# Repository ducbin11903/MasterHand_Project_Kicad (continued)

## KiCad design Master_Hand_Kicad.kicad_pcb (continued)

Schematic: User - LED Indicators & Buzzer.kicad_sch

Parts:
D9, D15, D16: RED 0402; LED0402-R-RD; MPN YLED0402G; LCSC Part C20608784
D10: ORANGE 0402; LED0402-R-RD; MPN YLED0402G; LCSC Part C20608784
D11: YELLOW 0402; LED0402-R-RD; MPN YLED0402G; LCSC Part C20608784
D12: GREEN 0402; LED0402-R-RD; MPN YLED0402G; LCSC Part C20608784
D13: BLUE 0402; LED0402-R-RD; MPN YLED0402G; LCSC Part C20608784
D14: WHITE 0402; LED0402-R-RD; MPN YLED0402G; LCSC Part C20608784
R59, R60, R65, R66: 330R 0.1%; R0402; MPN RT0402FRE07100KL; LCSC Part C728576
R61, R62, R63, R64: 100R 0.1%; R0402; MPN RT0402FRE07100KL; LCSC Part C728576

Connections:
+3V3: D9.1 (A), D10.1 (A), D11.1 (A), D12.1 (A), D13.1 (A), D14.1 (A), D15.1 (A), D16.1 (A); also elsewhere on the board
/Project Architecture/MCU - IOs/GPIO-LED_Debug_1: R65.1; also elsewhere on the board
/Project Architecture/MCU - IOs/GPIO-LED_Debug_2: R66.1; also elsewhere on the board
/Project Architecture/MCU - IOs/GPIO-LED_I: R59.1; also elsewhere on the board
/Project Architecture/MCU - IOs/GPIO-LED_M: R64.1; also elsewhere on the board
/Project Architecture/MCU - IOs/GPIO-LED_P: R62.1; also elsewhere on the board
/Project Architecture/MCU - IOs/GPIO-LED_R: R63.1; also elsewhere on the board
/Project Architecture/MCU - IOs/GPIO-LED_T1: R60.1; also elsewhere on the board
/Project Architecture/MCU - IOs/GPIO-LED_T2: R61.1; also elsewhere on the board
unnamed: D9.2 (K), R59.2
unnamed: D10.2 (K), R60.2
unnamed: D11.2 (K), R61.2
unnamed: D12.2 (K), R62.2
unnamed: D13.2 (K), R63.2
unnamed: D14.2 (K), R64.2
unnamed: D15.2 (K), R65.2
unnamed: D16.2 (K), R66.2

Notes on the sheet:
[${#}] ${SHEETNAME}

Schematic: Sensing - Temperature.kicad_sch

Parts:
C95: 100nF 50V; C0402; MPN CC0402KRX5R7BB105; LCSC Part C325464
R67, R68: 10K 0.1%; R0402; MPN RT0402FRE07100KL; LCSC Part C728576
U16: SHT40-N-NF; DFN-4_L1.5-W1.5-P0.80-TL-EP; MPN SHT40-N-NF; LCSC Part C54946589

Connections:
+3V3: C95.2, R67.1, R68.1, U16.3 (VDD); also elsewhere on the board
/Project Architecture/MCU - IOs/I2C-SCL: R68.2, U16.2 (SCL); also elsewhere on the board
/Project Architecture/MCU - IOs/I2C-SDA: R67.2, U16.1 (SDA); also elsewhere on the board
GND: C95.1, U16.4 (VSS); also elsewhere on the board

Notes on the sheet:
[${#}] ${SHEETNAME}

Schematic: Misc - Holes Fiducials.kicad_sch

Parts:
FM1, FM2, FM3: Fiducial_1mm_Mask2mm
H1, H2, H3: M2.4; MountingHole_2.4mm_M2.4_Pad_Via

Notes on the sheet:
[${#}] ${SHEETNAME}
Mounting Holes and Fiducial Markers

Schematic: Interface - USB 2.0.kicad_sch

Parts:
C83, C85: 4.7uF 50V; C0603; MPN CAP CER 0603; LCSC Part C14663
C84, C86: 100nF 50V; C0402; MPN CC0402KRX5R7BB105; LCSC Part C325464
D2, D5: BLUE 0402; LED0402-R-RD; MPN YLED0402G; LCSC Part C20608784
D3, D6: SMAJ5.0A; SMA_L4.3-W2.6-LS5.2-RD; MPN SMAJ5.0A; LCSC Part C83329
D4, D7: USBLC6-2SC6; SOT-23-6_L2.9-W1.6-P0.95-LS2.8-BL; MPN USBLC6-2SC6; LCSC Part C2827654
J9, J10: TYPE-C 16PIN 2MD; USB-C-SMD_TYPE-C-16PIN-2MD-073; MPN TYPE-C 16PIN 2MD(073); LCSC Part C2765186
R43, R48: 430K 0.1%; R0402; MPN RT0402FRE07100KL; LCSC Part C728576
R44, R49: 620K 0.1%; R0402; MPN RT0402FRE07100KL; LCSC Part C728576
R45, R50: 1K 0.1%; R0402; MPN RT0402FRE07100KL; LCSC Part C728576
R46, R47, R51, R52: 5.1K 0.1%; R0402; MPN RT0402FRE07100KL; LCSC Part C728576

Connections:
/Project Architecture/Interface - USB 2.0/USB1_N: D4.4 (IO2); also elsewhere on the board
/Project Architecture/Interface - USB 2.0/USB1_P: D4.6 (IO1); also elsewhere on the board
/Project Architecture/Interface - USB 2.0/USB2_N: D7.6 (IO1); also elsewhere on the board
/Project Architecture/Interface - USB 2.0/USB2_P: D7.4 (IO2); also elsewhere on the board
/Project Architecture/Interface - USB 2.0/VBUS_1: C83.2, C84.1, D3.1 (C), D4.5 (VBUS), J9.A4B9 (VBUS), J9.B4A9 (VBUS), R43.1, R45.1
/Project Architecture/Interface - USB 2.0/VBUS_2: C85.2, C86.1, D6.1 (C), D7.5 (VBUS), J10.A4B9 (VBUS), J10.B4A9 (VBUS), R48.1, R50.1
/Project Architecture/Interface - USB 2.0/VBUS_DET1: R43.2, R44.1; also elsewhere on the board
/Project Architecture/Interface - USB 2.0/VBUS_DET2: R48.2, R49.1; also elsewhere on the board
GND: C83.1, C84.2, C85.1, C86.2, D2.2 (K), D3.2 (A), D4.2 (GND), D5.2 (K), D6.2 (A), D7.2 (GND), J9.13 (EH), J9.14 (EH), J9.A1B12 (GND), J9.B1A12 (GND), J10.13 (EH), J10.14 (EH), J10.A1B12 (GND), J10.B1A12 (GND), R44.2, R46.2, R47.2, R49.2, R51.2, R52.2; also elsewhere on the board
unnamed: D2.1 (A), R45.2
unnamed: D5.1 (A), R50.2
unnamed: J9.A5 (CC1), R46.1
unnamed: J9.B5 (CC2), R47.1
unnamed: D4.3 (IO2), J9.A7 (Dn1), J9.B7 (Dn2)
unnamed: D4.1 (IO1), J9.A6 (Dp1), J9.B6 (Dp2)
unnamed: J10.A5 (CC1), R51.1
unnamed: J10.B5 (CC2), R52.1
unnamed: D7.1 (IO1), J10.A7 (Dn1), J10.B7 (Dn2)
unnamed: D7.3 (IO2), J10.A6 (Dp1), J10.B6 (Dp2)

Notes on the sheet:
[${#}] ${SHEETNAME}
DESIGN NOTE: [1] VBUS NOT connected to +5V/+3V3. Board is self-powered(LiPo). Sense + LED only. No backfeed to host. [2] LED direct from VBUS @ 1mA. USB2.0 suspend limit 2.5mA. LED 1mA + divider 33uA = 1.03mA (41%). Do NOT raise to 5mA. [3] VBUS_DET required - G474 has no dedicated VBUS pin. Self-p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

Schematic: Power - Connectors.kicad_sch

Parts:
C1, C2, C3, C4: 100nF 50V; C0603; MPN CAP CER 0603; LCSC Part C14663
J1: XT30PW-F; CONN-TH_XT30PW-F-1; MPN XT30PW-F20.G.Y; LCSC Part C2913282
J2: KF350-3.5-2P; CONN-TH_P3.50_KF350-3.5-2P; MPN KF350-3.5-2P; LCSC Part C474892
Q1, Q2: HV10N03; SOT-89-3_L4.5-W2.5-P1.50-LS4.0-BR; MPN HV10N03; LCSC Part C53329063
U1, U2: LM74700QDBVRQ1; SOT-23-6_L2.9-W1.6-P0.95-LS2.8-BL; MPN LM74700QDBVRQ1; LCSC Part C2941042

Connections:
+VBAT: Q1.3 (S), Q2.3 (S), U1.4 (CATHODE), U2.4 (CATHODE); also elsewhere on the board
/Project Architecture/Power - Connectors/+V_ADAPTER: C3.1, C4.1, J2.2, Q2.2 (D), U2.3 (EN), U2.6 (ANODE)
/Project Architecture/Power - Connectors/+V_BAT2S: C1.1, C2.1, J1.1, Q1.2 (D), U1.3 (EN), U1.6 (ANODE)
GND: C1.2, C3.2, J1.2, J2.1, U1.2 (GND), U2.2 (GND); also elsewhere on the board
unnamed: Q1.1 (G), U1.5 (GATE)
unnamed: Q2.1 (G), U2.5 (GATE)
unnamed: C2.2, U1.1 (VCAP)
unnamed: C4.2, U2.1 (VCAP)

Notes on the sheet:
[${#}] ${SHEETNAME}
Power Connectors - Path Control

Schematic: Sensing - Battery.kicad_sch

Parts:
C97: 100nF 50V; C0402; MPN CC0402KRX5R7BB105; LCSC Part C325464
R71: 100K 0.1%; R0402; MPN RT0402FRE07100KL; LCSC Part C728576
R72: 47K 0.1%; R0402; MPN RT0402FRE07100KL; LCSC Part C728576

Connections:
+VBAT: R71.2; also elsewhere on the board
/Project Architecture/MCU - IOs/SENSE_VBAT: C97.2, R71.1, R72.2; also elsewhere on the board
GND: C97.1, R72.1; also elsewhere on the board

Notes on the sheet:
Battery Voltage Sensing
[${#}] ${SHEETNAME}
DESIGN NOTE: Battery voltage sensing divider for 2S LiPo battery. R1 = 100kΩ (Top) R2 = 47kΩ (Bottom) Divider Ratio: VADC = VBAT × (47 / (100 + 47)) VADC = VBAT × 0.3197 2S LiPo: Max battery voltage (8.4V): 2.69 V Nominal voltage (7.4V): 2.37 V Low battery voltage (6.4V): 2.05 V Cutoff voltage (6.0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

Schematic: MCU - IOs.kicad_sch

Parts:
C43, C44, C45, C46: 8pF 16V; C0402; MPN CC0402KRX5R7BB105; LCSC Part C325464
U6, U7: STM32G474RET6; LQFP-64_L10.0-W10.0-P0.50-LS12.0-BL; MPN STM32G474RET6; LCSC Part C521608
X1, X2: X322516MLB4SI; CRYSTAL-SMD_4P-L3.2-W2.5-BL; MPN X322516MLB4SI; LCSC Part C13738

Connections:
/Project Architecture/Interface - FD-CAN/FDCAN1_RX: U6.34 (PB12); also elsewhere on the board
/Project Architecture/Interface - FD-CAN/FDCAN1_TX: U6.35 (PB13); also elsewhere on the board
/Project Architecture/Interface - FD-CAN/FDCAN2_RX: U7.34 (PB12); also elsewhere on the board
/Project Architecture/Interface - FD-CAN/FDCAN2_TX: U7.35 (PB13); also elsewhere on the board
/Project Architecture/Interface - Interconnects/NRST1: U6.7 (PG10); also elsewhere on the board
/Project Architecture/Interface - Interconnects/NRST2: U7.7 (PG10); also elsewhere on the board
/Project Architecture/Interface - Interconnects/SWCLK1: U6.50 (PA14); also elsewhere on the board
/Project Architecture/Interface - Interconnects/SWCLK2: U7.50 (PA14); also elsewhere on the board
/Project Architecture/Interface - Interconnects/SWDIO1: U6.49 (PA13); also elsewhere on the board
/Project Architecture/Interface - Interconnects/SWDIO2: U7.49 (PA13); also elsewhere on the board
/Project Architecture/Interface - Interconnects/USART1_CK1: U6.54 (PC12); also elsewhere on the board
/Project Architecture/Interface - Interconnects/USART1_CK2: U7.54 (PC12); also elsewhere on the board
/Project Architecture/Interface - Interconnects/USART1_RX1: U6.33 (PB11); also elsewhere on the board
/Project Architecture/Interface - Interconnects/USART1_RX2: U7.33 (PB11); also elsewhere on the board
/Project Architecture/Interface - Interconnects/USART1_TX1: U6.30 (PB10); also elsewhere on the board
/Project Architecture/Interface - Interconnects/USART1_TX2: U7.30 (PB10); also elsewhere on the board
/Project Architecture/Interface - USB 2.0/USB1_N: U6.45 (PA11); also elsewhere on the board
/Project Architecture/Interface - USB 2.0/USB1_P: U6.46 (PA12); also elsewhere on the board
/Project Architecture/Interface - USB 2.0/USB2_N: U7.45 (PA11); also elsewhere on the board
/Project Architecture/Interface - USB 2.0/USB2_P: U7.46 (PA12); also elsewhere on the board
/Project Architecture/Interface - USB 2.0/VBUS_DET1: U6.44 (PA10); also elsewhere on the board
/Project Architecture/Interface - USB 2.0/VBUS_DET2: U7.44 (PA10); also elsewhere on the board
/Project Architecture/MCU - IOs/BOARD_VERSION: U6.26 (PB2); also elsewhere on the board
/Project Architecture/MCU - IOs/BOOT_1: U6.61 (PB8); also elsewhere on the board
/Project Architecture/MCU - IOs/BOOT_2: U7.61 (PB8); also elsewhere on the board
/Project Architecture/MCU - IOs/DIAG_I: U6.3 (PC14); also elsewhere on the board
/Project Architecture/MCU - IOs/DIAG_M: U7.3 (PC14); also elsewhere on the board
/Project Architecture/MCU - IOs/DIAG_P: U7.37 (PB15); also elsewhere on the board
/Project Architecture/MCU - IOs/DIAG_R: U7.55 (PD2); also elsewhere on the board
/Project Architecture/MCU - IOs/DIAG_T1: U6.55 (PD2); also elsewhere on the board
/Project Architecture/MCU - IOs/DIAG_T2: U6.37 (PB15); also elsewhere on the board
/Project Architecture/MCU - IOs/ECA_I: U6.12 (PA0); also elsewhere on the board
/Project Architecture/MCU - IOs/ECA_M: U7.12 (PA0); also elsewhere on the board
/Project Architecture/MCU - IOs/ECA_P: U7.38 (PC6); also elsewhere on the board
/Project Architecture/MCU - IOs/ECA_R: U7.59 (PB6); also elsewhere on the board
/Project Architecture/MCU - IOs/ECA_T1: U6.59 (PB6); also elsewhere on the board
/Project Architecture/MCU - IOs/ECA_T2: U6.38 (PC6); also elsewhere on the board
/Project Architecture/MCU - IOs/ECB_I: U6.13 (PA1); also elsewhere on the board
/Project Architecture/MCU - IOs/ECB_M: U7.13 (PA1); also elsewhere on the board
/Project Architecture/MCU - IOs/ECB_P: U7.39 (PC7); also elsewhere on the board
/Project Architecture/MCU - IOs/ECB_R: U7.60 (PB7); also elsewhere on the board
/Project Architecture/MCU - IOs/ECB_T1: U6.60 (PB7); also elsewhere on the board
/Project Architecture/MCU - IOs/ECB_T2: U6.39 (PC7); also elsewhere on the board
/Project Architecture/MCU - IOs/ECC_I: U6.10 (PC2); also elsewhere on the board
/Project Architecture/MCU - IOs/ECC_M: U7.10 (PC2); also elsewhere on the board
/Project Architecture/MCU - IOs/ECC_P: U7.21 (PA7); also elsewhere on the board
/Project Architecture/MCU - IOs/ECC_R: U7.18 (PA4); also elsewhere on the board
/Project Architecture/MCU - IOs/ECC_T1: U6.18 (PA4); also elsewhere on the board
/Project Architecture/MCU - IOs/ECC_T2: U6.21 (PA7); also elsewhere on the board
/Project Architecture/MCU - IOs/EN_I: U6.9 (PC1); also elsewhere on the board
/Project Architecture/MCU - IOs/EN_M: U7.9 (PC1); also elsewhere on the board
/Project Architecture/MCU - IOs/EN_P: U7.23 (PC5); also elsewhere on the board
/Project Architecture/MCU - IOs/EN_R: U7.20 (PA6); also elsewhere on the board
/Project Architecture/MCU - IOs/EN_T1: U6.20 (PA6); also elsewhere on the board
/Project Architecture/MCU - IOs/EN_T2: U6.23 (PC5); also elsewhere on the board
/Project Architecture/MCU - IOs/GPIO-LED_Debug_1: U6.25 (PB1); also elsewhere on the board
/Project Architecture/MCU - IOs/GPIO-LED_Debug_2: U7.25 (PB1); also elsewhere on the board
/Project Architecture/MCU - IOs/GPIO-LED_I: U6.51 (PA15); also elsewhere on the board
/Project Architecture/MCU - IOs/GPIO-LED_M: U7.51 (PA15); also elsewhere on the board
/Project Architecture/MCU - IOs/GPIO-LED_P: U7.62 (PB9); also elsewhere on the board
/Project Architecture/MCU - IOs/GPIO-LED_R: U7.58 (PB5); also elsewhere on the board
/Project Architecture/MCU - IOs/GPIO-LED_T1: U6.58 (PB5); also elsewhere on the board
/Project Architecture/MCU - IOs/GPIO-LED_T2: U6.62 (PB9); also elsewhere on the board
/Project Architecture/MCU - IOs/I2C-SCL: U7.43 (PA9); also elsewhere on the board
/Project Architecture/MCU - IOs/I2C-SDA: U7.42 (PA8); also elsewhere on the board
/Project Architecture/MCU - IOs/MCU_ID1: U6.2 (PC13); also elsewhere on the board
/Project Architecture/MCU - IOs/MCU_ID2: U7.2 (PC13); also elsewhere on the board
/Project Architecture/MCU - IOs/OCM_I: U6.8 (PC0); also elsewhere on the board
/Project Architecture/MCU - IOs/OCM_M: U7.8 (PC0); also elsewhere on the board
/Project Architecture/MCU - IOs/OCM_P: U7.22 (PC4); also elsewhere on the board
/Project Architecture/MCU - IOs/OCM_R: U7.19 (PA5); also elsewhere on the board
/Project Architecture/MCU - IOs/OCM_T1: U6.19 (PA5); also elsewhere on the board
/Project Architecture/MCU - IOs/OCM_T2: U6.22 (PC4); also elsewhere on the board
/Project Architecture/MCU - IOs/OSC-IN_1: C43.1, U6.5 (PF0), X1.1 (OSC1)
/Project Architecture/MCU - IOs/OSC-IN_2: C45.1, U7.5 (PF0), X2.1 (OSC1)
/Project Architecture/MCU - IOs/OSC-OUT_1: C44.1, U6.6 (PF1), X1.3 (OSC2)
/Project Architecture/MCU - IOs/OSC-OUT_2: C46.1, U7.6 (PF1), X2.3 (OSC2)
/Project Architecture/MCU - IOs/PWMA_I: U6.17 (PA3); also elsewhere on the board
/Project Architecture/MCU - IOs/PWMA_M: U7.17 (PA3); also elsewhere on the board
/Project Architecture/MCU - IOs/PWMA_P: U7.41 (PC9); also elsewhere on the board
/Project Architecture/MCU - IOs/PWMA_R: U7.56 (PB3); also elsewhere on the board
/Project Architecture/MCU - IOs/PWMA_T1: U6.56 (PB3); also elsewhere on the board
/Project Architecture/MCU - IOs/PWMA_T2: U6.41 (PC9); also elsewhere on the board
/Project Architecture/MCU - IOs/PWMB_I: U6.14 (PA2); also elsewhere on the board
/Project Architecture/MCU - IOs/PWMB_M: U7.14 (PA2); also elsewhere on the board
/Project Architecture/MCU - IOs/PWMB_P: U7.40 (PC8); also elsewhere on the board
/Project Architecture/MCU - IOs/PWMB_R: U7.57 (PB4); also elsewhere on the board
/Project Architecture/MCU - IOs/PWMB_T1: U6.57 (PB4); also elsewhere on the board
/Project Architecture/MCU - IOs/PWMB_T2: U6.40 (PC8); also elsewhere on the board
/Project Architecture/MCU - IOs/SENSE_VBAT: U7.26 (PB2); also elsewhere on the board
/Project Architecture/MCU - IOs/UART_RX: U6.53 (PC11), U7.52 (PC10)
/Project Architecture/MCU - IOs/UART_TX: U6.52 (PC10), U7.53 (PC11)
GND: C43.2, C44.2, C45.2, C46.2, X1.2 (GND), X1.4 (GND), X2.2 (GND), X2.4 (GND); also elsewhere on the board

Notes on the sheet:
MCU 2
MD Pinky
MCU 1
MD Thumb 1
MD Thumb 2
LEDs
USB PORT
MCB to MB - I2C
Battery Voltage Sense
Buzzer
MD Index
Out of Density to Place TP
MD Ring
MD Middle
Temperature and Humidity
SWD (Debug) Port
5Mbps FD-CAN Bus
Board Version Selection
MCU ID
[${#}] ${SHEETNAME}
SWITCH
Motor Driver
DESIGN NOTE: We use the LQFP64 version to have extra pins for controlling an external fan.
LAYOUT NOTE: Footprint deviates from datasheet and IPC7351 to allow for soldermask sliver between pads according to PCBWay design rules.
Oscillator HSE
MCB to MB - USART
Test Points
DESIGN NOTE: Do not forget to flash option bytes when flashing for the first time.

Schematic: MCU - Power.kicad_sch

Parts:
C25, C31, C32, C34, C40, C41: 1uF 16V; C0402; MPN CC0402KRX5R7BB105; LCSC Part C325464
C26, C35: 4.7uF 16V; C0402; MPN CC0402KRX5R7BB105; LCSC Part C325464
C27, C28, C29, C30, C33, C36, C37, C38, C39, C42: 100nF 50V; C0402; MPN CC0402KRX5R7BB105; LCSC Part C325464
FB1, FB2: 1k @ 100MHz; L0805; MPN PBBHAQ2012H-102T10; LCSC Part C52178237
U6, U7: STM32G474RET6; LQFP-64_L10.0-W10.0-P0.50-LS12.0-BL; MPN STM32G474RET6; LCSC Part C521608

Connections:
+3V3: C25.1, C26.1, C27.1, C28.1, C29.1, C30.1, C34.1, C35.1, C36.1, C37.1, C38.1, C39.1, U6.1 (VBAT), U6.16 (VDD), U6.32 (VDD), U6.48 (VDD), U6.64 (VDD), U7.1 (VBAT), U7.16 (VDD), U7.32 (VDD), U7.48 (VDD), U7.64 (VDD); also elsewhere on the board
+A3V3: C31.1, C40.1, FB1.1, FB2.1; also elsewhere on the board
GND: C25.2, C26.2, C27.2, C28.2, C29.2, C30.2, C31.2, C32.2, C33.2, C34.2, C35.2, C36.2, C37.2, C38.2, C39.2, C40.2, C41.2, C42.2, U6.15 (VSS), U6.27 (VSSA), U6.31 (VSS), U6.47 (VSS), U6.63 (VSS), U7.15 (VSS), U7.27 (VSSA), U7.31 (VSS), U7.47 (VSS), U7.63 (VSS); also elsewhere on the board
unnamed: C32.1, C33.1, FB1.2, U6.28 (VREF+), U6.29 (VDDA)
unnamed: C41.1, C42.1, FB2.2, U7.28 (VREF+), U7.29 (VDDA)

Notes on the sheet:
Microcontroller Power Supply Scheme
LAYOUT NOTE: Place each capacitor close to the relevant pin. Minimize loop inductance.

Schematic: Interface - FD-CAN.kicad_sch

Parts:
C87, C88, C89, C90: 100nF 50V; C0402; MPN CC0402KRX5R7BB105; LCSC Part C325464
R53, R54: 10K 0.1%; R0402; MPN RT0402FRE07100KL; LCSC Part C728576
U14, U15: TJA1051T/3; SOP-8_L4.9-W3.9-P1.27-LS6.0-BL-1; MPN TJA1051T/3; LCSC Part C5342108

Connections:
+3V3: C88.1, C90.1, R53.1, R54.2, U14.5 (VIO), U15.5 (VIO); also elsewhere on the board
+5V: C87.1, C89.1, U14.3 (VCC), U15.3 (VCC); also elsewhere on the board
/Project Architecture/Interface - FD-CAN/FDCAN1_RX: U15.4 (RXD); also elsewhere on the board
/Project Architecture/Interface - FD-CAN/FDCAN1_TX: R54.1, U15.1 (TXD); also elsewhere on the board
/Project Architecture/Interface - FD-CAN/FDCAN2_RX: U14.4 (RXD); also elsewhere on the board
/Project Architecture/Interface - FD-CAN/FDCAN2_TX: R53.2, U14.1 (TXD); also elsewhere on the board
/Project Architecture/Interface - FD-CAN/FDCAN_N: U14.6 (CANL), U15.6 (CANL); also elsewhere on the board
/Project Architecture/Interface - FD-CAN/FDCAN_P: U14.7 (CANH), U15.7 (CANH); also elsewhere on the board
GND: C87.2, C88.2, C89.2, C90.2, U14.2 (GND), U14.8 (S), U15.2 (GND), U15.8 (S); also elsewhere on the board

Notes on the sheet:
LAYOUT NOTE: We decided to route it further away to minimize risk of ground lift on the RX/TX lines due to high currents.
DESIGN NOTE: Silent mode disabled. Pin "S" to ground.
Fault Protected FD-CAN Transceiver
LAYOUT NOTE: Place close to FD-CAN connector if possible to reduce stub length.
DESIGN NOTE: 120-ohm termination in Interconnects sheet.
[${#}] ${SHEETNAME}

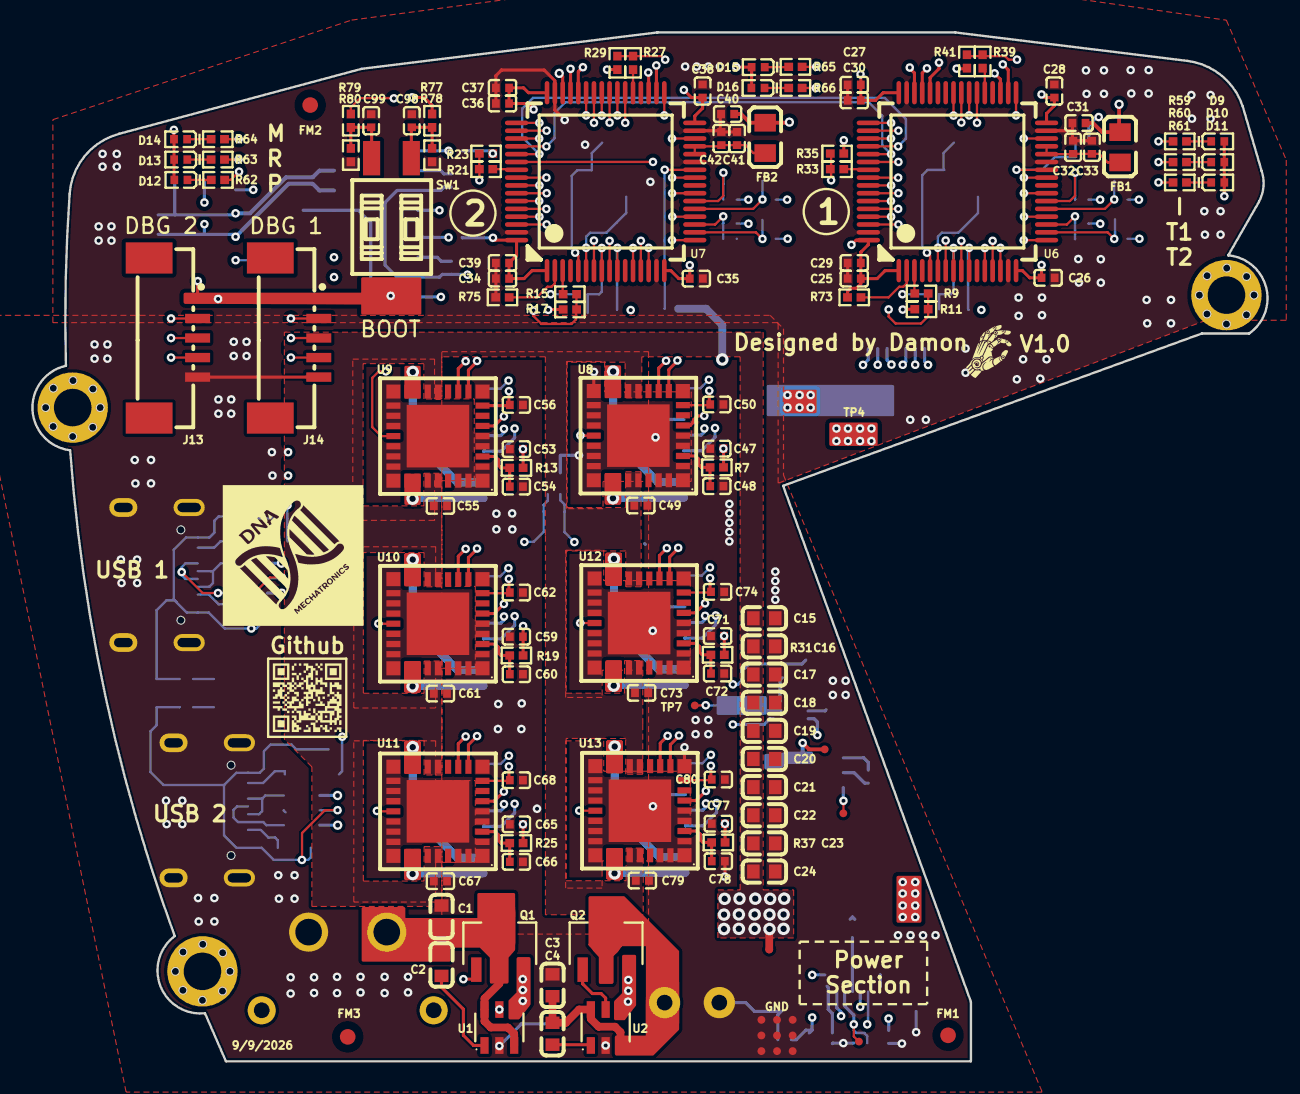
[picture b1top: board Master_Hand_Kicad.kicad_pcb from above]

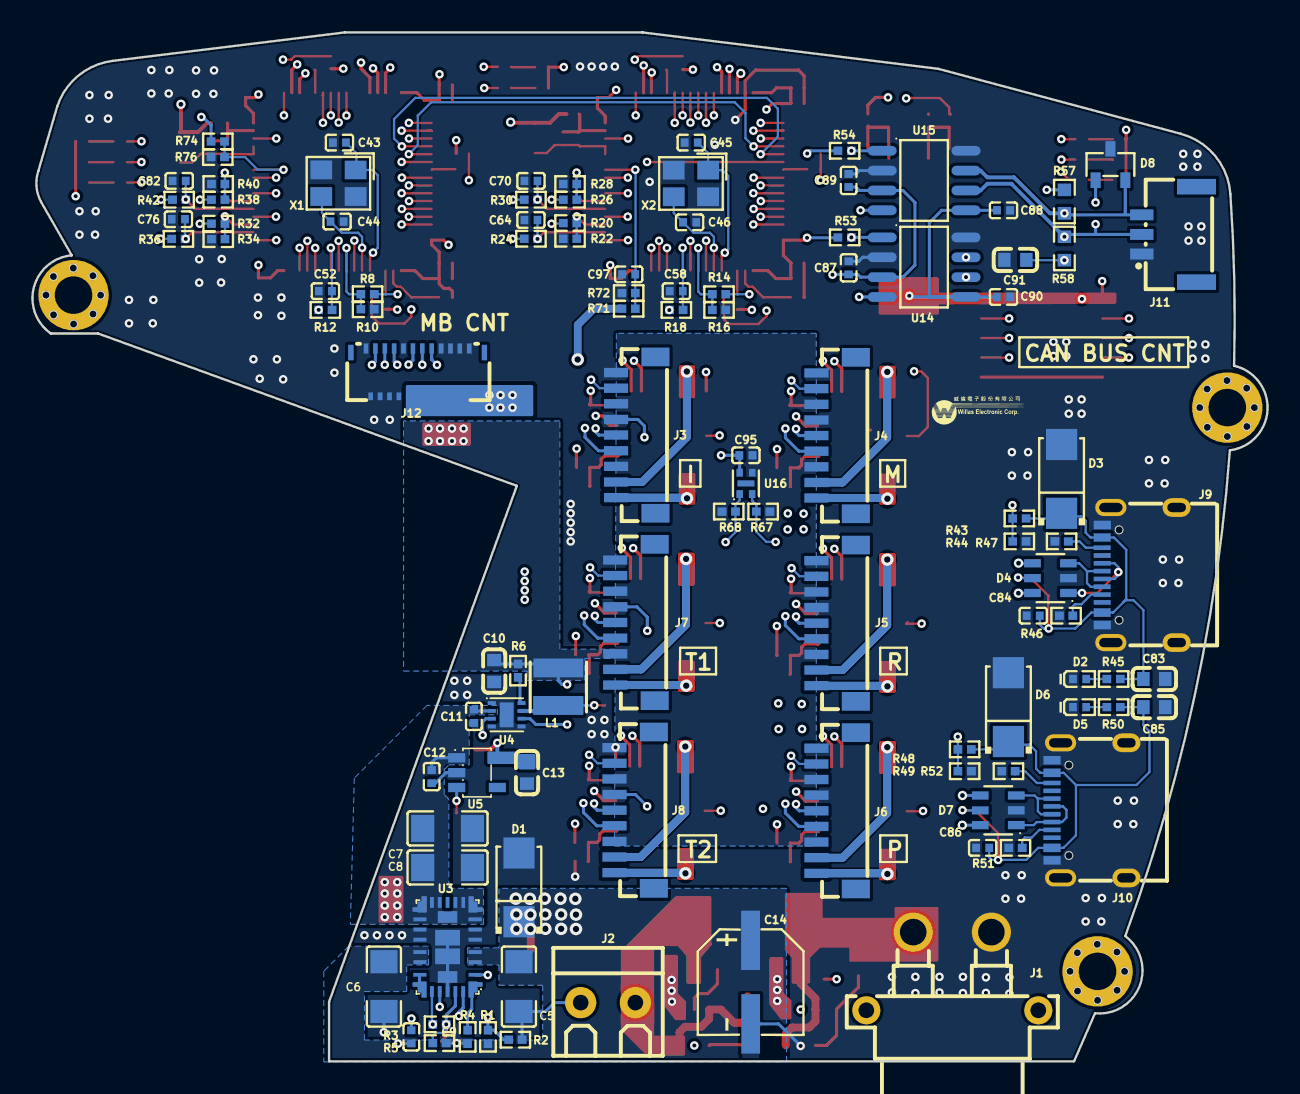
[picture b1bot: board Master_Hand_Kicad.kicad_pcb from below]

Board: 6 copper layers, 79.0 x 65.8 mm, 232 parts (104 on the bottom side), 174 nets.

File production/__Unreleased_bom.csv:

Designator,Footprint,Quantity,Value,LCSC Part #
"C1, C2, C3, C4",C0603,4,100nF 50V,C14663
C10,C0603,1,22uF 50V,C14663
C11,C0402,1,10uF 50V,C325464
"C12, C9",C0402,2,1uF 50V,C325464
C13,C0603,1,1uF 50V,C14663
C14,CAP-SMD_BD6.3-L6.6-W6.6-FD-1,1,SM337M025E0800,C44606382
"C15, C16, C17, C18, C19, C20, C21, C22, C23, C24",C0603,10,10uF 50V,C14663
"C25, C31, C32, C34, C40, C41",C0402,6,1uF 16V,C325464
"C26, C35",C0402,2,4.7uF 16V,C325464
"C27, C28, C29, C30, C33, C36, C37, C38, C39, C42, C48, C49, C52, C54, C55, C58, C60, C61, C64, C66, C67, C70, C72, C73, C76, C78, C79, C82, C84, C86, C87, C88, C89, C90, C95, C97, C98, C99",C0402,38,100nF 50V,C325464
"C43, C44, C45, C46",C0402,4,8pF 16V,C325464
"C47, C53, C59, C65, C71, C77",C0402,6,4.7uF 50V,C325464
"C5, C6",C1206,2,4.7uF 100V,C132170
"C50, C56, C62, C68, C74, C80",C0402,6,470nF 50V,C325464
C7,C1206,1,10uF 50V,C132170
C8,C1206,1,100nF 50V,C132170
"C83, C85, C91",C0603,3,4.7uF 50V,C14663
D1,SMA_L4.3-W2.6-LS5.2-RD,1,SMAJ12A,C148213
D10,LED0402-R-RD,1,ORANGE 0402,C20608784
D11,LED0402-R-RD,1,YELLOW 0402,C20608784
D12,LED0402-R-RD,1,GREEN 0402,C20608784
"D13, D2, D5",LED0402-R-RD,3,BLUE 0402,C20608784
D14,LED0402-R-RD,1,WHITE 0402,C20608784
"D15, D16, D9",LED0402-R-RD,3,RED 0402,C20608784
"D3, D6",SMA_L4.3-W2.6-LS5.2-RD,2,SMAJ5.0A,C83329
"D4, D7",SOT-23-6_L2.9-W1.6-P0.95-LS2.8-BL,2,USBLC6-2SC6,C2827654
D8,SOT-23-3_L2.9-W1.3-P1.90-LS2.4-BR,1,PESD1CAN,C21713981
"FB1, FB2",L0805,2,1k @ 100MHz,C52178237
"FM1, FM2, FM3",Fiducial_1mm_Mask2mm,3,~,
J1,CONN-TH_XT30PW-F-1,1,XT30PW-F,C2913282
"J10, J9",USB-C-SMD_TYPE-C-16PIN-2MD-073,2,TYPE-C 16PIN 2MD,C2765186
J11,CONN-SMD_3P-P1.25_SHOU_1.25-3PLTDK,1,1.25-3PLTDK,C3008548
J12,FPC-SMD_23P-P0.60_502598-2393,1,5025982393,C7021254
"J13, J14",CONN-SMD_5P-P1.25_HCZZ0015-5,2,HCZZ0015-5,C7433471
J2,CONN-TH_P3.50_KF350-3.5-2P,1,KF350-3.5-2P,C474892
"J3, J4, J5, J6, J7, J8",CONN-SMD_9P-P1.00_BM09B-SRSS-TB,6,BM09B-SRSS-TB,C160395
L1,IND-SMD_L3.0-W3.0_SMNR3015,1,ANR3015T2R2M,C6364793
"Q1, Q2",SOT-89-3_L4.5-W2.5-P1.50-LS4.0-BR,2,HV10N03,C53329063
R1,R0402,1,41.2K 0.1%,C728576
"R10, R12, R15, R16, R18, R21, R22, R24, R27, R28, R30, R33, R34, R36, R39, R40, R42, R9",R0402,18,220R 0.1%,C728576
"R11, R14, R17, R20, R23, R26, R29, R32, R35, R38, R41, R45, R50, R8",R0402,14,1K 0.1%,C728576
"R13, R19, R25, R31, R37, R7",R0402,6,1R 0.1%,C728576
"R2, R5, R53, R54, R67, R68, R77, R78, R79, R80",R0402,10,10K 0.1%,C728576
R3,R0402,1,40.2K 0.1%,C728576
R4,R0402,1,13K 0.1%,C728576
"R43, R48",R0402,2,430K 0.1%,C728576
"R44, R49",R0402,2,620K 0.1%,C728576
"R46, R47, R51, R52",R0402,4,5.1K 0.1%,C728576
"R57, R58",R0603,2,60R4 0.1%,C4107493
"R59, R60, R65, R66",R0402,4,330R 0.1%,C728576
"R6, R71, R74, R76",R0402,4,100K 0.1%,C728576
"R61, R62, R63, R64",R0402,4,100R 0.1%,C728576
R72,R0402,1,47K 0.1%,C728576
"R73, R75",R0402,2,0R 0.1%,C728576
SW1,SW-SMD_DSIC02LSGET,1,DSIC02LSGET,C3293152
"TP1, TP2, TP3, TP4, TP5, TP6, TP7",TestPoint_Pad_D0.5mm,7,~,
"U1, U2",SOT-23-6_L2.9-W1.6-P0.95-LS2.8-BL,2,LM74700QDBVRQ1,C2941042
"U10, U11, U12, U13, U8, U9",UQFN-28_L6.0-W6.0-P0.65-BL-EP4.0,6,"TB9051FTG,EL",C2150635
"U14, U15",SOP-8_L4.9-W3.9-P1.27-LS6.0-BL-1,2,TJA1051T/3,C5342108
U16,DFN-4_L1.5-W1.5-P0.80-TL-EP,1,SHT40-N-NF,C54946589
U3,QFN-30_L6.0-W4.0-P0.50_TLVM13630RDHR,1,TPSM63603RDHR,C5219327
U4,WSON-8_L2.0-W2.0-P0.50-TL-EP,1,TPS62162DSG,C40256
U5,SOT-23-5_L3.0-W1.7-P0.95-LS2.8-BR,1,TLV75533PDBVR,C404027
"U6, U7",LQFP-64_L10.0-W10.0-P0.50-LS12.0-BL,2,STM32G474RET6,C15742
"X1, X2",CRYSTAL-SMD_4P-L3.2-W2.5-BL,2,X322516MLB4SI,C13738

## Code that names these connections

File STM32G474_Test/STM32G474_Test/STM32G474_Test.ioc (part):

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Mcu.Name=STM32G474R(B-C-E)Tx
Mcu.Package=LQFP64
Mcu.UserName=STM32G474RETx
PA0.Signal=S_TIM2_CH1
PA1.Signal=S_TIM2_CH2
PA10.Signal=GPIO_Input
PA11.Mode=Device
PA11.Signal=USB_DM
PA12.Mode=Device
PA12.Signal=USB_DP
PA13.Mode=Serial_Wire
PA13.Signal=SYS_JTMS-SWDIO
PA14.Mode=Serial_Wire
PA14.Signal=SYS_JTCK-SWCLK
PA15.Signal=GPIO_Output
PA2.Signal=S_TIM15_CH1
PA3.Signal=S_TIM15_CH2
PA4.Mode=IN17-Single-Ended
PA4.Signal=ADC2_IN17
PA5.Mode=IN13-Single-Ended
PA5.Signal=ADC2_IN13
PA6.Signal=GPIO_Output
PA7.Mode=IN4-Single-Ended
PA7.Signal=ADC2_IN4
PA8.Mode=I2C
PA8.Signal=I2C2_SDA
PA9.Mode=I2C
PA9.Signal=I2C2_SCL
PB1.Signal=GPIO_Output
PB10.Mode=Synchronous
PB10.Signal=USART3_TX
PB11.Mode=Synchronous
PB11.Signal=USART3_RX
PB12.Mode=FDCAN_Activate
PB12.Signal=FDCAN2_RX
PB13.Mode=FDCAN_Activate
PB13.Signal=FDCAN2_TX
PB15.Signal=GPIO_Input
PB2.Signal=ADC2_IN12
PB3.Signal=TIM8_CH1N
PB4.Signal=TIM8_CH2N
PB5.Signal=GPIO_Output
PB6.Signal=S_TIM4_CH1
PB7.Signal=S_TIM4_CH2
PB9.GPIOParameters=GPIO_Label
PB9.GPIO_Label=PWM_BUZZER
PB9.Signal=S_TIM17_CH1
PC0.Mode=IN6-Single-Ended
PC0.Signal=ADC1_IN6
PC1.Signal=GPIO_Output
PC10.Mode=Asynchronous
PC10.Signal=UART4_TX
PC11.Mode=Asynchronous
PC11.Signal=UART4_RX
PC12.Mode=Synchronous
PC12.Signal=USART3_CK
PC2.Mode=IN8-Single-Ended
PC2.Signal=ADC1_IN8
PC3.Signal=GPIO_Input
PC4.Mode=IN5-Single-Ended
PC4.Signal=ADC2_IN5
PC5.Signal=GPIO_Output
PC6.GPIOParameters=GPIO_Label
PC6.GPIO_Label=ECB
PC6.Signal=S_TIM3_CH1
PC7.GPIOParameters=GPIO_Label
PC7.GPIO_Label=ECA
PC7.Signal=S_TIM3_CH2
PC8.GPIOParameters=GPIO_Label
PC8.GPIO_Label=PWMA
PC8.Signal=S_TIM8_CH3
PC9.GPIOParameters=GPIO_Label
PC9.GPIO_Label=PWMB
PC9.Signal=S_TIM8_CH4
PD2.Signal=GPIO_Input
PF0-OSC_IN.Mode=HSE-External-Oscillator
PF0-OSC_IN.Signal=RCC_OSC_IN
PF1-OSC_OUT.Mode=HSE-External-Oscillator
PF1-OSC_OUT.Signal=RCC_OSC_OUT
RCC.HSE_VALUE=16000000
RCC.SYSCLKFreq_VALUE=80000000
RCC.SYSCLKSource=RCC_SYSCLKSOURCE_PLLCLK
board=custom

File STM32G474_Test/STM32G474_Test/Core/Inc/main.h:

/* USER CODE BEGIN Header */
/**
  ******************************************************************************
  * @file           : main.h
  * @brief          : Header for main.c file.
  *                   This file contains the common defines of the application.
  ******************************************************************************
  * @attention
  *
  * Copyright (c) 2026 STMicroelectronics.
  * All rights reserved.
  *
  * This software is licensed under terms that can be found in the LICENSE file
  * in the root directory of this software component.
  * If no LICENSE file comes with this software, it is provided AS-IS.
  *
  ******************************************************************************
  */
/* USER CODE END Header */

/* Define to prevent recursive inclusion -------------------------------------*/
#ifndef __MAIN_H
#define __MAIN_H

#ifdef __cplusplus
extern "C" {
#endif

/* Includes ------------------------------------------------------------------*/
#include "stm32g4xx_hal.h"

/* Private includes ----------------------------------------------------------*/
/* USER CODE BEGIN Includes */

/* USER CODE END Includes */

/* Exported types ------------------------------------------------------------*/
/* USER CODE BEGIN ET */

/* USER CODE END ET */

/* Exported constants --------------------------------------------------------*/
/* USER CODE BEGIN EC */

/* USER CODE END EC */

/* Exported macro ------------------------------------------------------------*/
/* USER CODE BEGIN EM */

/* USER CODE END EM */

/* Exported functions prototypes ---------------------------------------------*/
void Error_Handler(void);

/* USER CODE BEGIN EFP */

/* USER CODE END EFP */

/* Private defines -----------------------------------------------------------*/
#define DIAG_T2_Pin GPIO_PIN_13
#define DIAG_T2_GPIO_Port GPIOC
#define DIAG_T1_Pin GPIO_PIN_14
#define DIAG_T1_GPIO_Port GPIOC
#define DIAG_I_Pin GPIO_PIN_15
#define DIAG_I_GPIO_Port GPIOC
#define PWMA_T2_Pin GPIO_PIN_0
#define PWMA_T2_GPIO_Port GPIOC
#define PWMB_T2_Pin GPIO_PIN_1
#define PWMB_T2_GPIO_Port GPIOC
#define PWMA_T1_Pin GPIO_PIN_2
#define PWMA_T1_GPIO_Port GPIOC
#define PWMB_T1_Pin GPIO_PIN_3
#define PWMB_T1_GPIO_Port GPIOC
#define ECA_T2_Pin GPIO_PIN_0
#define ECA_T2_GPIO_Port GPIOA
#define ECB_T2_Pin GPIO_PIN_1
#define ECB_T2_GPIO_Port GPIOA
#define OCM_T2_Pin GPIO_PIN_2
#define OCM_T2_GPIO_Port GPIOA
#define OCM_T1_Pin GPIO_PIN_3
#define OCM_T1_GPIO_Port GPIOA
#define ECC_T2_Pin GPIO_PIN_4
#define ECC_T2_GPIO_Port GPIOA
#define ECC_T1_Pin GPIO_PIN_5
#define ECC_T1_GPIO_Port GPIOA
#define ECA_T1_Pin GPIO_PIN_6
#define ECA_T1_GPIO_Port GPIOA
#define ECB_T1_Pin GPIO_PIN_7
#define ECB_T1_GPIO_Port GPIOA
#define ECC_I_Pin GPIO_PIN_4
#define ECC_I_GPIO_Port GPIOC
#define SENSE_VBAT_Pin GPIO_PIN_5
#define SENSE_VBAT_GPIO_Port GPIOC
#define OCM_I_Pin GPIO_PIN_0
#define OCM_I_GPIO_Port GPIOB
#define EN_I_Pin GPIO_PIN_1
#define EN_I_GPIO_Port GPIOB
#define BOARD_VERSION_Pin GPIO_PIN_2
#define BOARD_VERSION_GPIO_Port GPIOB
#define EN_IB10_Pin GPIO_PIN_10
#define EN_IB10_GPIO_Port GPIOB
#define PWMA_I_Pin GPIO_PIN_14
#define PWMA_I_GPIO_Port GPIOB
#define PWMB_I_Pin GPIO_PIN_15
#define PWMB_I_GPIO_Port GPIOB
#define ECA_I_Pin GPIO_PIN_6
#define ECA_I_GPIO_Port GPIOC
#define ECB_I_Pin GPIO_PIN_7
#define ECB_I_GPIO_Port GPIOC
#define LED_DEBUG_Pin GPIO_PIN_10
#define LED_DEBUG_GPIO_Port GPIOA
#define LED_T2_Pin GPIO_PIN_15
#define LED_T2_GPIO_Port GPIOA
#define LED_T1_Pin GPIO_PIN_10
#define LED_T1_GPIO_Port GPIOC
#define LED_I_Pin GPIO_PIN_11
#define LED_I_GPIO_Port GPIOC
#define MCU_ID_Pin GPIO_PIN_12
#define MCU_ID_GPIO_Port GPIOC
#define EN_T1_Pin GPIO_PIN_2
#define EN_T1_GPIO_Port GPIOD
#define PWM_BUZZER_Pin GPIO_PIN_9
#define PWM_BUZZER_GPIO_Port GPIOB

/* USER CODE BEGIN Private defines */

/* USER CODE END Private defines */

#ifdef __cplusplus
}
#endif

#endif /* __MAIN_H */

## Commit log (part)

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2026-06-23 [23/06/2026] Block Diagram update
2026-06-24 [24/06/2026] Block Diagram Update
2026-06-24 [25/06/2026][MCU-POWER] Update
2026-06-25 [25/06/2025][Block Diagram] Update
2026-06-25 [25/06/2025][MCU - IOs] Update
2026-06-26 [26/06/2026][MCU - IOs] Update
